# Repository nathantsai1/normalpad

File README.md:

# NormalPad

*Note: this is a hackboard, not a hackpad
## What is this?
This is a 75% keyboard inspired by the [Keychron Q1 Custom Keyboard](https://www.keychron.com/products/keychron-q1?srsltid=AfmBOorYcrgbMnQshTxcVkn31a3YPq6My79lAXlqjA35xHALWIpRg0Ld). It consists of 82 keys, hot-swappable switches a 3D printable case, and stabilizers. The bottom half is split in half to make it easier to sand

## Quick overview of repo
+ cad
    1. full_keyboard.stl
+ firmware
    1. normalPad.ino
+ pcb
    1. hackpad_v2.kicad_pcb
    2. hackpad_v2.kicad_prl
    3. hackpad_v2.kicad_pro
    4. hackpad_v2.kicad_sch
+ production
    + cad(stl)
        1. plate.stl
        2. upper_ex.stl
        3. bottom.stl
    1. normalPad.ino
    2. gerbers-zip.zip
+ src
    1. angle_bottom.png
    2. assembled_bottom.png
    3. bottom.png
    4. diagram.png
    5. pcb.png
    6. plate.png
    7. schem.png
    8. side_short.png
    9. side_long.png
    10. together.png
    11. top_plate.png
+ README.md
+ bom.csv
+ JOURNAL.md

*The more important files are contained in the production folder, README, and bom(in a ccsv file and at the end of this page)
## Why did I make this
I primarily started this for [HackPad v2](https://hackpad.hackclub.com/keyboard). However, during the process of making this, I learned more about the different types of switches, stabilizers, splitting up CAD designs into multiple parts, and all the parts of the keyboard. I learned a little bit more about the [Arduino Keyboard library](https://docs.arduino.cc/language-reference/en/functions/usb/Keyboard/), how to write relatively efficient code, and organize my pcb schematic and pcb in a larger scale than what I previously learned. As I had taken a break for a few months from my original keyboard design, I had stopped 

## Pictures of my design:
### Schematic:
<b>My diagram, which depicts the row and column numbers</b>

<b>The schematic for the pcb, relatively organized in the order wanted</b>

### PCB
<b>My PCB</b>

<b>PCB back</b>

<b>PCB front (w/key switch side)</b>

### CAD Case(Disassembled)
From top to bottom 

<b>Top plate</b>

<b>Plate</b>

<b>Bottom</b>

### CAD case(relatively assembled)

<b>Assembled case</b>

<b>Side analysis of case</b>

<b>sketch of designsadded to project</b>
in order: back case, front case, front pcb

## Bill of Materials
Also see [here](./BOM.csv)
|mfg name|	            Description|	        Price|	shipping|	total|	notes|
| ---|                          ---|              ---|      ---|     ---|    ---|
|ALIEXPRESS|	        [keycap set](https://www.aliexpress.us/item/3256803996370867.html)|	            9.23|	0|	    9.23| |
|ALIEXPRESS|	        [keyswitch(90)](https://www.aliexpress.us/item/3256807160745636.html)|	        25.17|	0|	        25.17| |
|ALIEXPRESS|	        taxes|	                0|	0|	        0| |
| | | | | | |
|JLCPCB|	            pcb|	                20.9|	17.13|	    38.03| |
| | | | | | |
|MECHANICAL KEYBOARD|    [hot swap(90)](https://mechanicalkeyboards.com/products/kailh-switch-hot-swap-socket)|	        9.9|   	5.8|	    15.15| |
|MECHANIAL KEYBOARDS|   [stabilizer](https://mechanicalkeyboards.com/products/durock-v3-pcb-mount-screw-in-stabilizer-tkl-kit)|	            15|	    6.27|	    21.27| |
| | | | | | |
|DIGIKEY|	            [Raspberry pi pico w/o header](https://www.digikey.com/en/products/detail/raspberry-pi/SC0915/13624793)|	    5|  	0|	        5| |
|DIGIKEY|	            [pin header 1x40](https://www.digikey.com/en/products/detail/amphenol-cs-commercial-products/G800W268018EU/17083164)|	    0.8|	|	        0.8| |
|DIGIKEY|	            [bolts(2Mx0.4 - 8mm*18)](https://www.digikey.com/en/products/detail/essentra-components/50M020040P008/11639927)|	1.76|	0|	        1.76| |
|DIGIKEY|	            [diode(84)](https://www.digikey.com/en/products/detail/comchip-technology/1N4001-G/1979654)|	            4.54|	0|	        4.54| |
|DIGIKEY|	            total(tariff+tax, shipping)|	        1.57|	4.99|	    6.56| |
|CAD CASE|	            cad case|	                |	|	        5.51| |
Total (with case and PCB): 133.02
Total (without case and PCB) 89.48
*PRICES IN USD

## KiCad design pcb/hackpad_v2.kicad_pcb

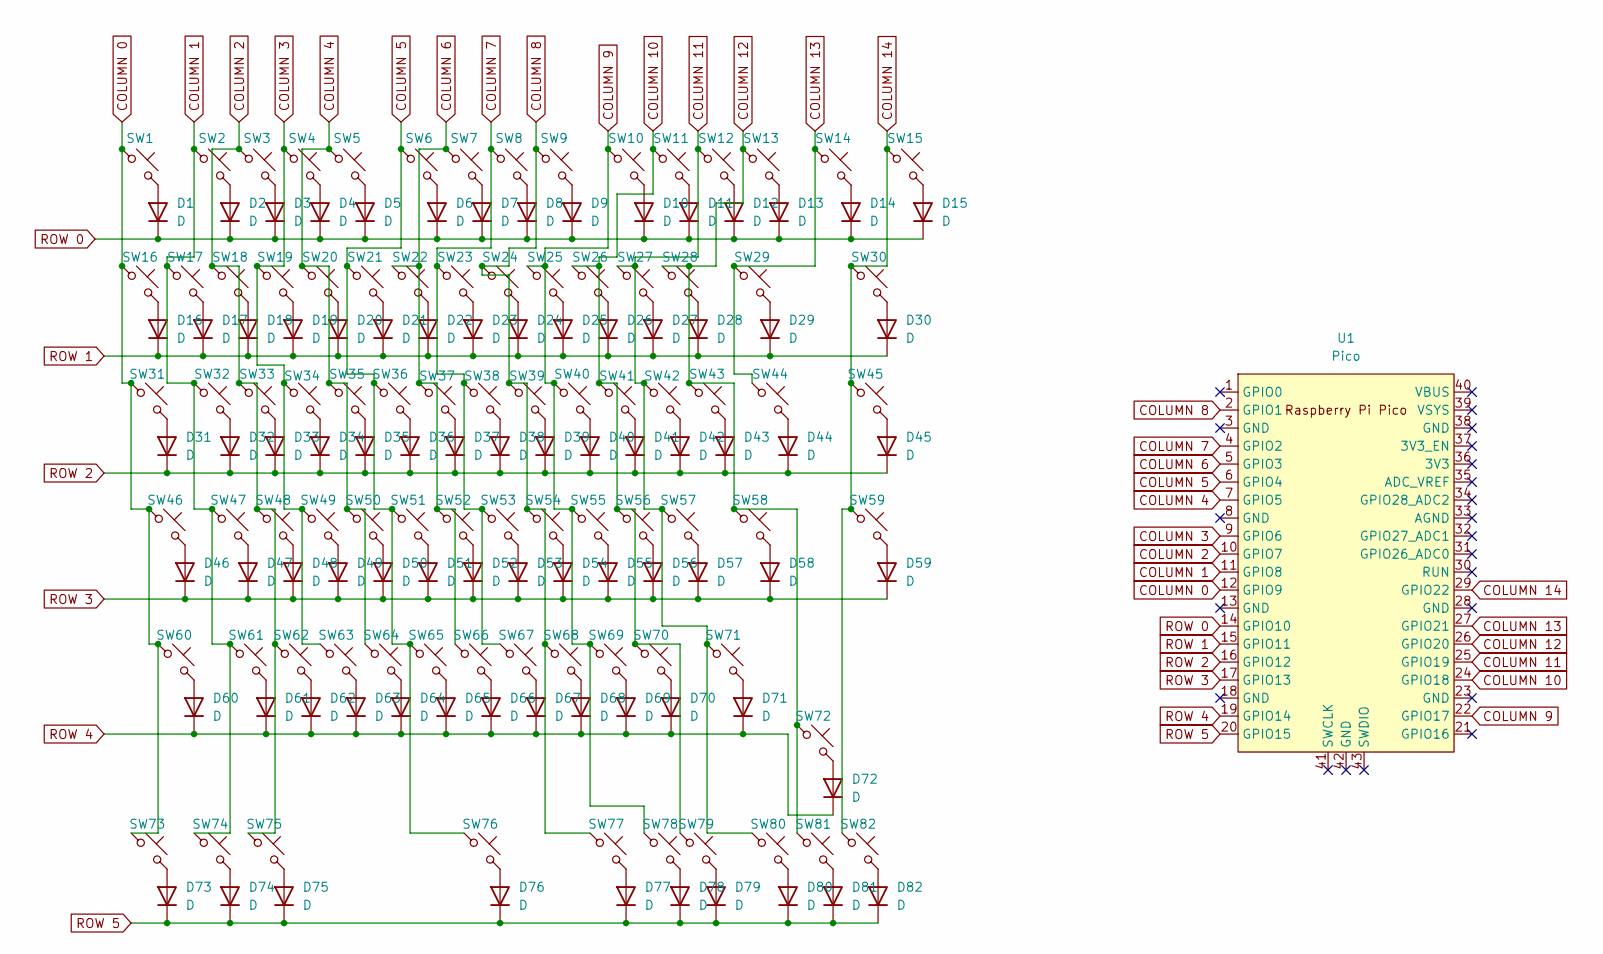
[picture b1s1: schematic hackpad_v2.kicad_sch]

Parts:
D1, D2, D3, D4, D5, D6, D7, D8, D9, D10, D11, D12, D13, D14, D15, D16, D17, D18, D19, D20, D21, D22, D23, D24, D25, D26, D27, D28, D29, D30, D31, D32, D33, D34, D35, D36, D37, D38, D39, D40, D41, D42, D43, D44, D45, D46, D47, D48, D49, D50, D51, D52, D53, D54, D55, D56, D57, D58, D59, D60, D61, D62, D63, D64, D65, D66, D67, D68, D69, D70, D71, D72, D73, D74, D75, D76, D77, D78, D79, D80, D81, D82: D; D_DO-41_SOD81_P10.16mm_Horizontal
SW1, SW2, SW3, SW4, SW5, SW6, SW7, SW8, SW9, SW10, SW11, SW12, SW13, SW14, SW15, SW16, SW17, SW18, SW19, SW20, SW21, SW22, SW23, SW24, SW25, SW26, SW27, SW28, SW30, SW32, SW33, SW34, SW35, SW36, SW37, SW38, SW39, SW40, SW41, SW42, SW43, SW45, SW47, SW48, SW49, SW50, SW51, SW52, SW53, SW54, SW55, SW56, SW57, SW59, SW61, SW62, SW63, SW64, SW65, SW66, SW67, SW68, SW69, SW70, SW72, SW77, SW78, SW79, SW80, SW81, SW82: SW_Push_45deg; MX-Hotswap-1U
SW29: SW_Push_45deg; MX-Hotswap-2U
SW31, SW44: SW_Push_45deg; MX-Hotswap-1.5U
SW46, SW71: SW_Push_45deg; MX-Hotswap-1.75U
SW58, SW60: SW_Push_45deg; MX-Hotswap-2.25U
SW73, SW74, SW75: SW_Push_45deg; MX-Hotswap-1.25U
SW76: SW_Push_45deg; MX-Hotswap-6.25U
U1: Pico; RPi_Pico_SMD_TH

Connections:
COLUMN 0: SW1.1, SW16.1, SW31.1, SW46.1, SW60.1, SW73.1, U1.12 (GPIO9)
COLUMN 1: SW2.1, SW17.1, SW32.1, SW47.1, SW61.1, SW74.1, U1.11 (GPIO8)
COLUMN 2: SW3.1, SW18.1, SW33.1, SW48.1, SW62.1, SW75.1, U1.10 (GPIO7)
COLUMN 3: SW4.1, SW19.1, SW34.1, SW49.1, SW63.1, U1.9 (GPIO6)
COLUMN 4: SW5.1, SW20.1, SW35.1, SW50.1, SW64.1, U1.7 (GPIO5)
COLUMN 5: SW6.1, SW21.1, SW36.1, SW51.1, SW65.1, SW76.1, U1.6 (GPIO4)
COLUMN 6: SW7.1, SW22.1, SW37.1, SW52.1, SW66.1, U1.5 (GPIO3)
COLUMN 7: SW8.1, SW23.1, SW38.1, SW53.1, SW67.1, U1.4 (GPIO2)
COLUMN 8: SW9.1, SW24.1, SW39.1, SW54.1, SW68.1, SW77.1, U1.2 (GPIO1)
COLUMN 9: SW10.1, SW25.1, SW40.1, SW55.1, SW69.1, SW78.1, U1.22 (GPIO17)
COLUMN 10: SW11.1, SW26.1, SW41.1, SW56.1, SW70.1, SW79.1, U1.24 (GPIO18)
COLUMN 11: SW12.1, SW27.1, SW42.1, SW57.1, SW71.1, SW80.1, U1.25 (GPIO19)
COLUMN 12: SW13.1, SW28.1, SW43.1, SW58.1, SW72.1, SW81.1, U1.26 (GPIO20)
COLUMN 13: SW14.1, SW29.1, SW44.1, U1.27 (GPIO21)
COLUMN 14: SW15.1, SW30.1, SW45.1, SW59.1, SW82.1, U1.29 (GPIO22)
unnamed: D1.2 (A), SW1.2
unnamed: D2.2 (A), SW2.2
unnamed: D3.2 (A), SW3.2
unnamed: D4.2 (A), SW4.2
unnamed: D5.2 (A), SW5.2
unnamed: D6.2 (A), SW6.2
unnamed: D7.2 (A), SW7.2
unnamed: D8.2 (A), SW8.2
unnamed: D9.2 (A), SW9.2
unnamed: D10.2 (A), SW10.2
unnamed: D11.2 (A), SW11.2
unnamed: D12.2 (A), SW12.2
unnamed: D13.2 (A), SW13.2
unnamed: D14.2 (A), SW14.2
unnamed: D15.2 (A), SW15.2
unnamed: D16.2 (A), SW16.2
unnamed: D17.2 (A), SW17.2
unnamed: D18.2 (A), SW18.2
unnamed: D19.2 (A), SW19.2
unnamed: D20.2 (A), SW20.2
unnamed: D21.2 (A), SW21.2
unnamed: D22.2 (A), SW22.2
unnamed: D23.2 (A), SW23.2
unnamed: D24.2 (A), SW24.2
unnamed: D25.2 (A), SW25.2
unnamed: D26.2 (A), SW26.2
unnamed: D27.2 (A), SW27.2
unnamed: D28.2 (A), SW28.2
unnamed: D29.2 (A), SW29.2
unnamed: D30.2 (A), SW30.2
unnamed: D31.2 (A), SW31.2
unnamed: D32.2 (A), SW32.2
unnamed: D33.2 (A), SW33.2
unnamed: D34.2 (A), SW34.2
unnamed: D35.2 (A), SW35.2
unnamed: D36.2 (A), SW36.2
unnamed: D37.2 (A), SW37.2
unnamed: D38.2 (A), SW38.2
unnamed: D39.2 (A), SW39.2
unnamed: D40.2 (A), SW40.2
unnamed: D41.2 (A), SW41.2
unnamed: D42.2 (A), SW42.2
unnamed: D43.2 (A), SW43.2
unnamed: D44.2 (A), SW44.2
unnamed: D45.2 (A), SW45.2
unnamed: D46.2 (A), SW46.2
unnamed: D47.2 (A), SW47.2
unnamed: D48.2 (A), SW48.2
unnamed: D49.2 (A), SW49.2
unnamed: D50.2 (A), SW50.2
unnamed: D51.2 (A), SW51.2
unnamed: D52.2 (A), SW52.2
unnamed: D53.2 (A), SW53.2
unnamed: D54.2 (A), SW54.2
unnamed: D55.2 (A), SW55.2
unnamed: D56.2 (A), SW56.2
unnamed: D57.2 (A), SW57.2
unnamed: D58.2 (A), SW58.2
unnamed: D59.2 (A), SW59.2
unnamed: D60.2 (A), SW60.2
unnamed: D61.2 (A), SW61.2
unnamed: D62.2 (A), SW62.2
unnamed: D63.2 (A), SW63.2
unnamed: D64.2 (A), SW64.2
unnamed: D65.2 (A), SW65.2
unnamed: D66.2 (A), SW66.2
unnamed: D67.2 (A), SW67.2
unnamed: D68.2 (A), SW68.2
unnamed: D69.2 (A), SW69.2
unnamed: D70.2 (A), SW70.2
unnamed: D71.2 (A), SW71.2
unnamed: D72.2 (A), SW72.2
unnamed: D73.2 (A), SW73.2
unnamed: D74.2 (A), SW74.2
unnamed: D75.2 (A), SW75.2
unnamed: D76.2 (A), SW76.2
unnamed: D77.2 (A), SW77.2
unnamed: D78.2 (A), SW78.2
unnamed: D79.2 (A), SW79.2
unnamed: D80.2 (A), SW80.2
unnamed: D81.2 (A), SW81.2
unnamed: D82.2 (A), SW82.2
ROW 0: D1.1 (K), D2.1 (K), D3.1 (K), D4.1 (K), D5.1 (K), D6.1 (K), D7.1 (K), D8.1 (K), D9.1 (K), D10.1 (K), D11.1 (K), D12.1 (K), D13.1 (K), D14.1 (K), D15.1 (K), U1.14 (GPIO10)
ROW 1: D16.1 (K), D17.1 (K), D18.1 (K), D19.1 (K), D20.1 (K), D21.1 (K), D22.1 (K), D23.1 (K), D24.1 (K), D25.1 (K), D26.1 (K), D27.1 (K), D28.1 (K), D29.1 (K), D30.1 (K), U1.15 (GPIO11)
ROW 2: D31.1 (K), D32.1 (K), D33.1 (K), D34.1 (K), D35.1 (K), D36.1 (K), D37.1 (K), D38.1 (K), D39.1 (K), D40.1 (K), D41.1 (K), D42.1 (K), D43.1 (K), D44.1 (K), D45.1 (K), U1.16 (GPIO12)
ROW 3: D46.1 (K), D47.1 (K), D48.1 (K), D49.1 (K), D50.1 (K), D51.1 (K), D52.1 (K), D53.1 (K), D54.1 (K), D55.1 (K), D56.1 (K), D57.1 (K), D58.1 (K), D59.1 (K), U1.17 (GPIO13)
ROW 4: D60.1 (K), D61.1 (K), D62.1 (K), D63.1 (K), D64.1 (K), D65.1 (K), D66.1 (K), D67.1 (K), D68.1 (K), D69.1 (K), D70.1 (K), D71.1 (K), D72.1 (K), U1.19 (GPIO14)
ROW 5: D73.1 (K), D74.1 (K), D75.1 (K), D76.1 (K), D77.1 (K), D78.1 (K), D79.1 (K), D80.1 (K), D81.1 (K), D82.1 (K), U1.20 (GPIO15)

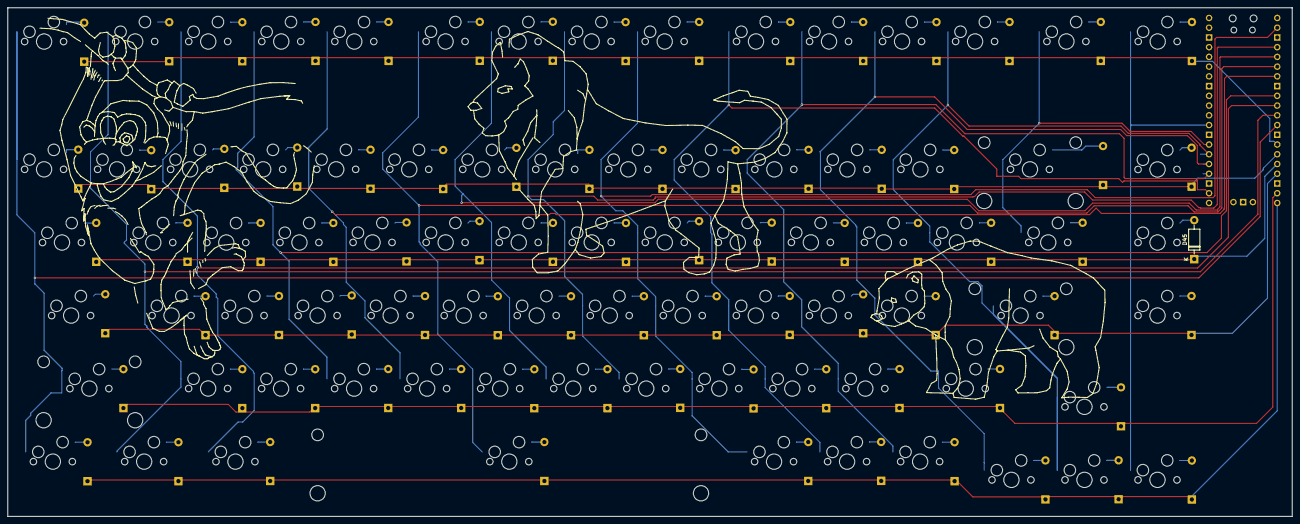
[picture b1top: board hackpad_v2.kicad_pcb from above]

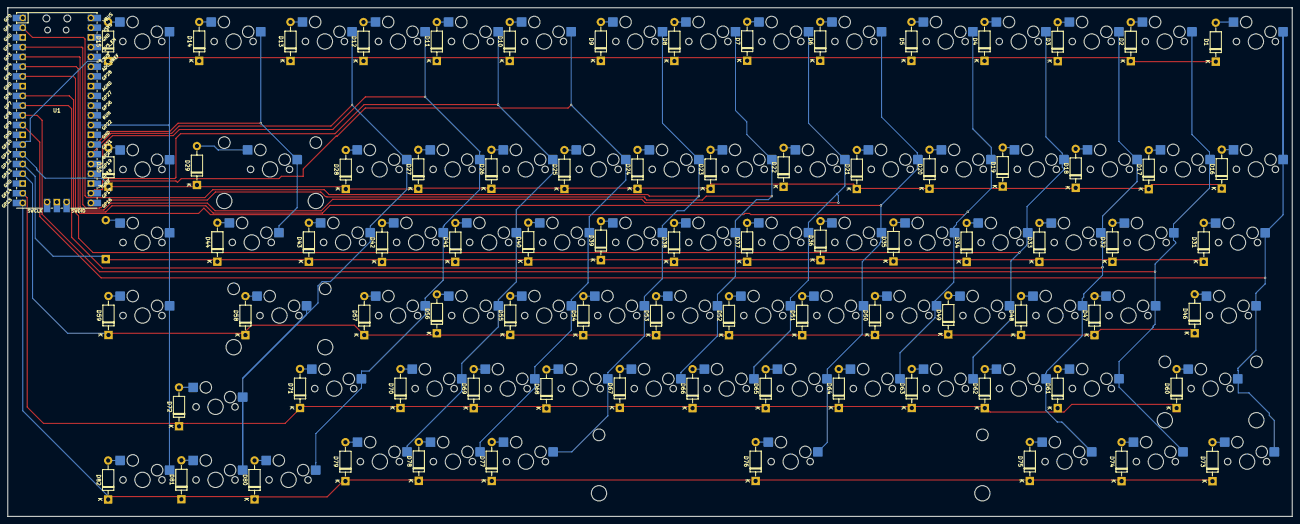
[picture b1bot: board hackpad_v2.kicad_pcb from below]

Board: 2 copper layers, 335.0 x 132.7 mm, 165 parts (164 on the bottom side), 103 nets.

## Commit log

2025-06-29 fix mds
2025-06-29 update journal
2025-07-02 fix highway issues
2025-07-05 change design
2025-07-05 change design
    so much work!
2025-07-06 change stuff
2025-07-08 change pcb zip file
2025-07-09 fix bom's
2025-07-09 add total to BOM
2025-07-09 add time to jounral
2025-11-23 improve journal and software
